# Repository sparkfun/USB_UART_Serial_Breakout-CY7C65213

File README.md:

SparkFun USB UART Serial Breakout - CY7C65213
==================

[*SparkFun USB UART Serial Breakout - CY7C65213*](https://www.sparkfun.com/products/13830)

The CY7C65213 USB to UART serial breakout is designed to provide users with a means to access all available I/O pins on the IC, and to provide a 6-pin UART header that is compatible with other SparkFun breakout boards. This breakout has a microUSB connector and other support circuitry to get the IC quickly up and running.

Repository Contents
-------------------

* **/hardware** - Eagle PCB layout files
* **/Production** - Files to support SparkFun production

Documentation
-------------------

[Hookup Guide](https://learn.sparkfun.com/tutorials/sparkfun-usb-uart-breakout-cy7c65213-hookup-guide) - Basic hookup guide

License Information
-------------------

All contents of this repository are released under [Creative Commons Share-alike 4.0](http://creativecommons.org/licenses/by-sa/4.0/).

Authors: Mike Hord @ SparkFun Electonics

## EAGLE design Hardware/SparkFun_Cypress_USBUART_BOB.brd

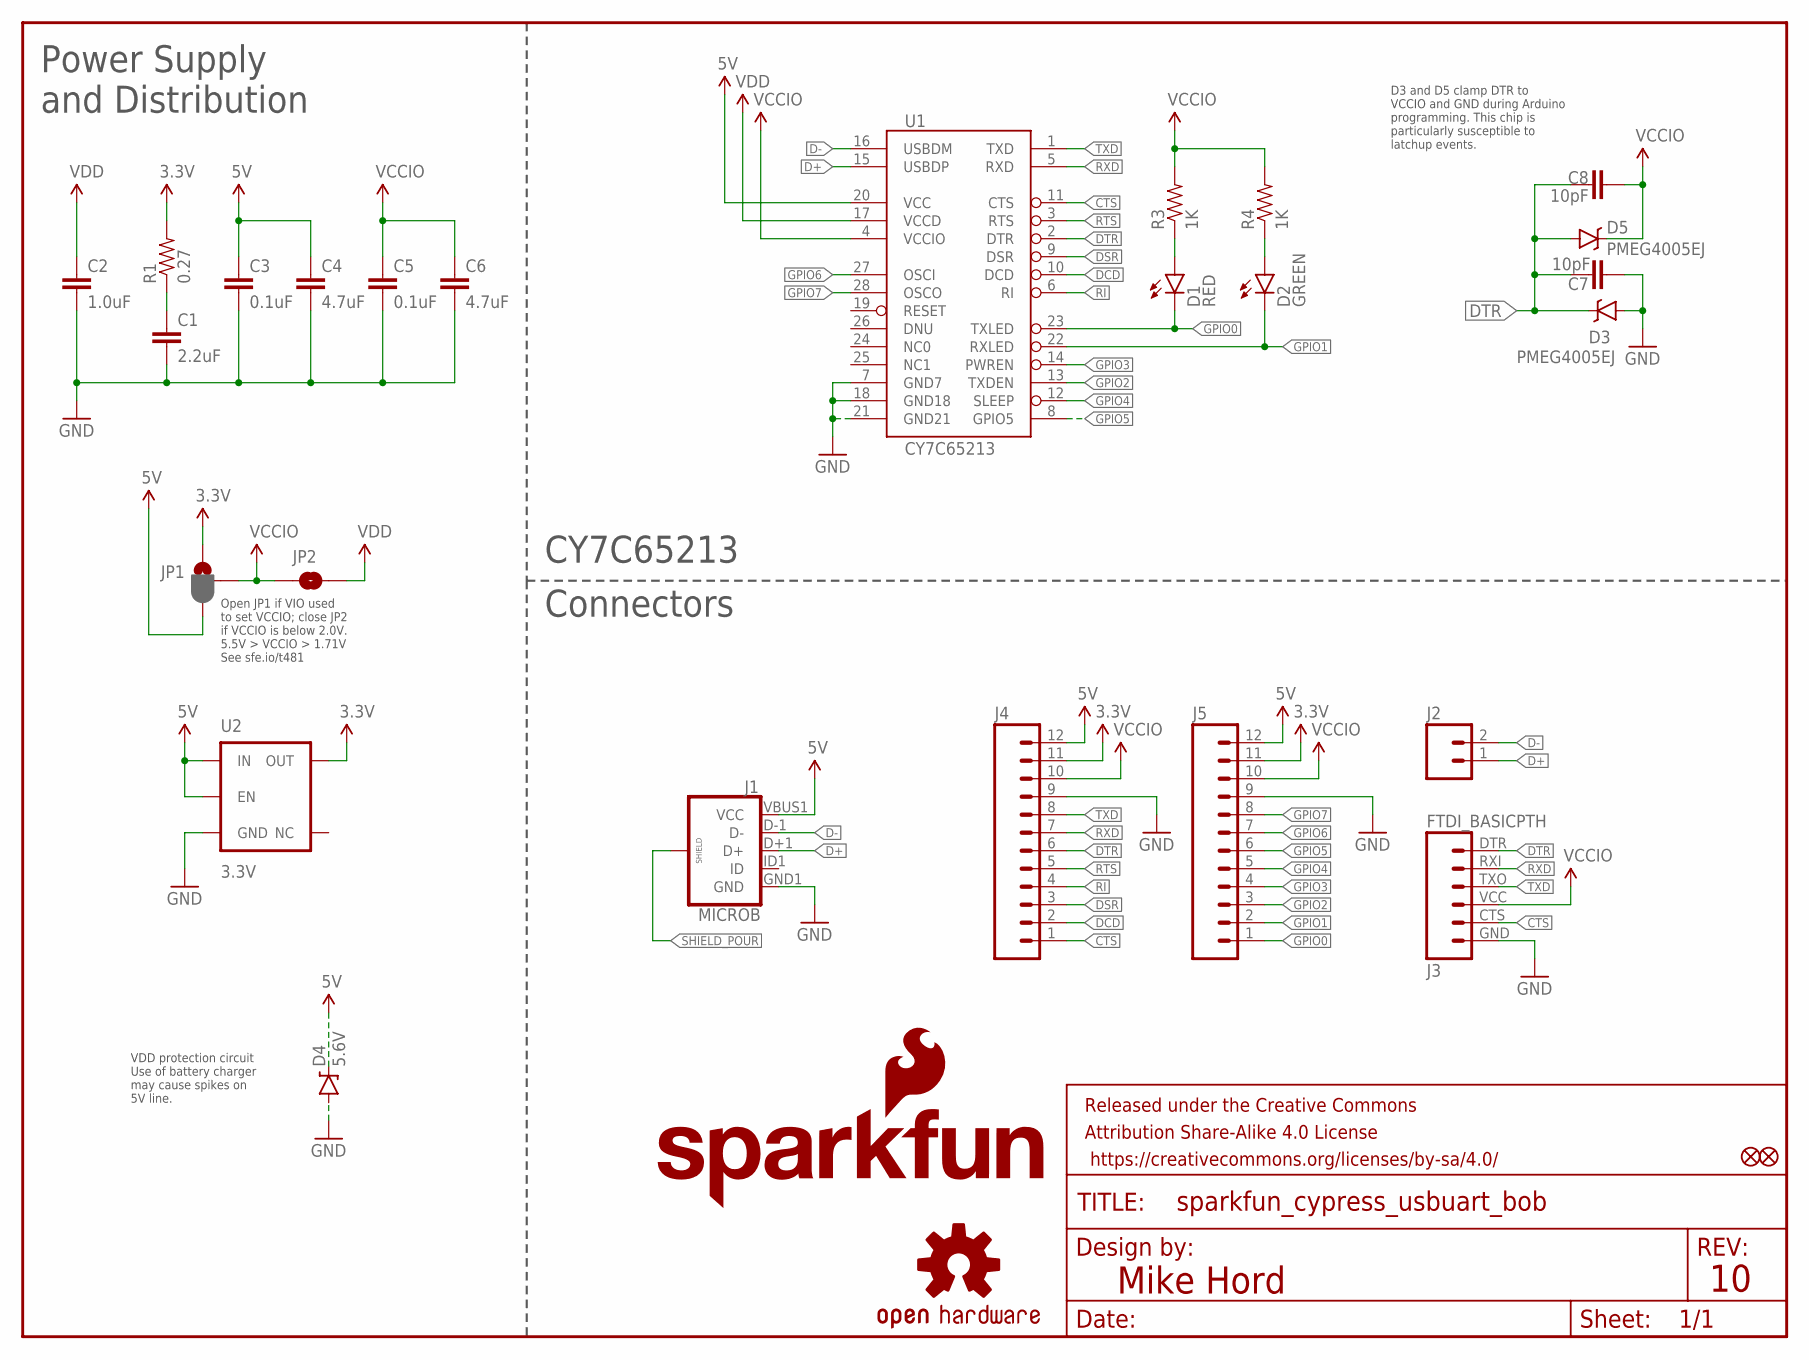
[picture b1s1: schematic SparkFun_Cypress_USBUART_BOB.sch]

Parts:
C1: 2.2uF; 0603-CAP
C2: 1.0uF; 0603-CAP
C3, C5: 0.1uF; 0603-CAP
C4, C6: 4.7uF; 1206-CAP
C7, C8: 10pF; 0603-CAP
D1: RED; LED-0603
D2: GREEN; LED-0603
D3, D5: PMEG4005EJ; SOD-323
D4: 5.6V; SOD-323
FD1, FD2: FIDUCIALUFIDUCIAL; MICRO-FIDUCIAL
FRAME1: FRAME-LETTER; CREATIVE_COMMONS
J1: MICROB; USB-B-MICRO-SMD_V03
J2: M02PTH; 1X02
J3: FTDI_BASICPTH; FTDI_BASIC
J4, J5: M12PTH; 1X12
JP1: JUMPER-PAD-3-2OF3_NC_BY_PASTE; PAD-JUMPER-3-2OF3_NC_BY_PASTE_YES_SILK_FULL_BOX
JP2: JUMPER-PAD-2-NOYES_SILK; PAD-JUMPER-2-NO_YES_SILK
LOGO1: SFE_LOGO_NAME_FLAME.1_INCH; SFE_LOGO_NAME_FLAME_.1
LOGO2: OSHW-LOGOS; OSHW-LOGO-S
R1: 0.27; 0603-RES
R3, R4: 1K; 0603-RES
U1: CY7C65213; SSOP28DB
U2: 3.3V; SOT23-5

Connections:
3.3V: J4.11, J5.11, JP1.1, R1.2, U2.5 (OUT)
5V: C3.1, C4.1, D4.C, J1.VBUS1 (VCC), J4.12, J5.12, JP1.3, U1.20 (VCC), U2.1 (IN), U2.3 (EN)
CTS: J3.CTS (5), J4.1, U1.11 (CTS)
D+: J1.D+1 (D+), J2.1, U1.15 (USBDP)
D-: J1.D-1 (D-), J2.2, U1.16 (USBDM)
DCD: J4.2, U1.10 (DCD)
DSR: J4.3, U1.9 (DSR)
DTR: C7.1, C8.1, D3.C, D5.A, J3.DTR (1), J4.6, U1.2 (DTR)
GND: C1.2, C2.2, C3.2, C4.2, C5.2, C6.2, C7.2, D3.A, D4.A, J1.GND1 (GND), J3.GND (6), J4.9, J5.9, U1.7 (GND7), U1.18 (GND18), U1.21 (GND21), U2.2 (GND)
GPIO0: D1.C, J5.1, U1.23 (TXLED)
GPIO1: D2.C, J5.2, U1.22 (RXLED)
GPIO2: J5.3, U1.13 (TXDEN)
GPIO3: J5.4, U1.14 (PWREN)
GPIO4: J5.5, U1.12 (SLEEP)
GPIO5: J5.6, U1.8 (GPIO5)
GPIO6: J5.7, U1.27 (OSCI)
GPIO7: J5.8, U1.28 (OSCO)
unnamed: C1.1, R1.1
unnamed: D2.A, R4.1
unnamed: D1.A, R3.1
NC1: U1.25 (NC1)
RI: J4.4, U1.6 (RI)
RTS: J4.5, U1.3 (RTS)
RXD: J3.RXI (2), J4.7, U1.5 (RXD)
SHIELD_POUR: J1.SHIELD1 (SHIELD), J1.SHIELD2 (SHIELD), J1.SHIELD3 (SHIELD)
TXD: J3.TXO (3), J4.8, U1.1 (TXD)
VCCIO: C5.1, C6.1, C8.2, D5.C, J3.VCC (4), J4.10, J5.10, JP1.2, JP2.1, R3.2, R4.2, U1.4 (VCCIO)
VDD: C2.1, JP2.2, U1.17 (VCCD)

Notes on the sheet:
Mike Hord
Open JP1 if VIO used to set VCCIO; close JP2 if VCCIO is below 2.0V. 5.5V > VCCIO > 1.71V See sfe.io/t481
Power Supply and Distribution
Connectors
CY7C65213
D3 and D5 clamp DTR to VCCIO and GND during Arduino programming. This chip is particularly susceptible to latchup events.
VDD protection circuit Use of battery charger may cause spikes on 5V line.

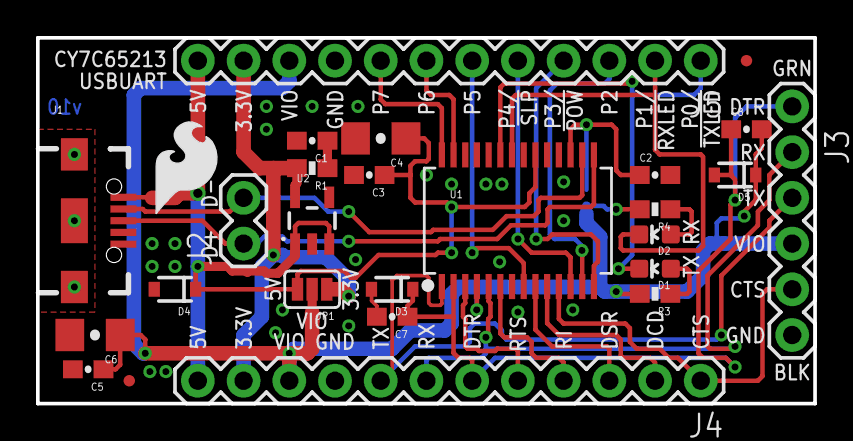
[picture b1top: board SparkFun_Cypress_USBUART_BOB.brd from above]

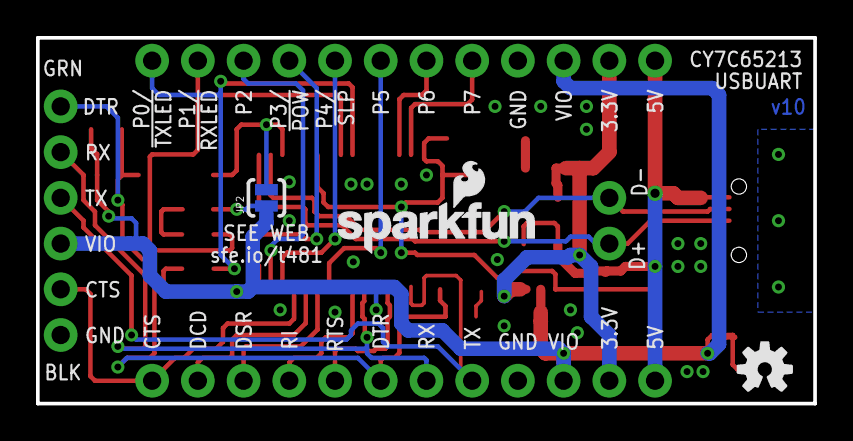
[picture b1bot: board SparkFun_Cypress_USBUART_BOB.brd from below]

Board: 2 copper layers, 43.2 x 20.3 mm, 31 parts (3 on the bottom side), 27 nets.

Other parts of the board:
LOGO5: SFE_LOGO_FLAME.2_INCH; SFE_LOGO_FLAME_.2

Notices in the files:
parts and their libraries:
SparkFun-Capacitors: Licensing: Creative Commons ShareAlike 4.0 International - https://creativecommons.org/licenses/by-sa/4.0
SparkFun-Aesthetics: Released under the Creative Commons Attribution Share-Alike 4.0 License
SparkFun-Aesthetics: https://creativecommons.org/licenses/by-sa/4.0
